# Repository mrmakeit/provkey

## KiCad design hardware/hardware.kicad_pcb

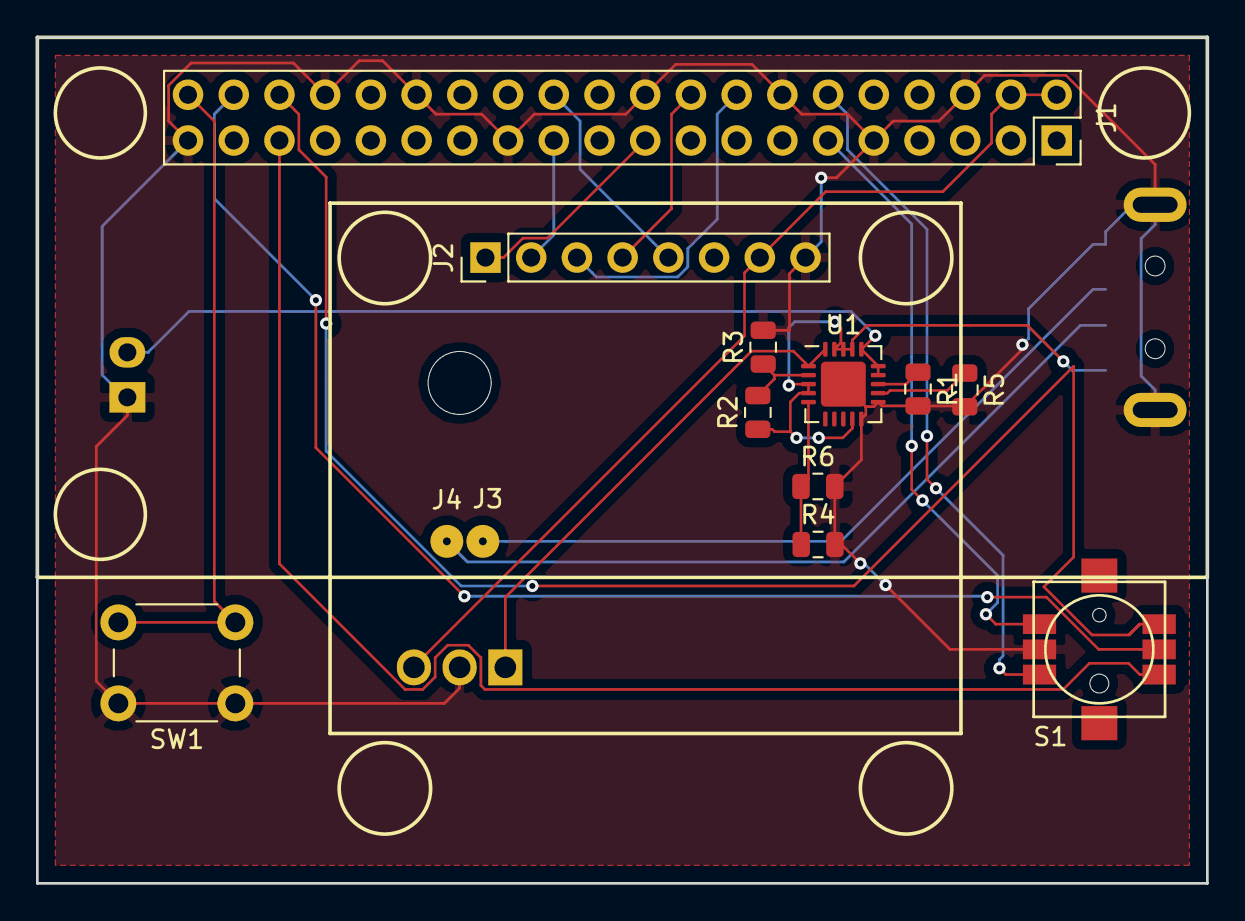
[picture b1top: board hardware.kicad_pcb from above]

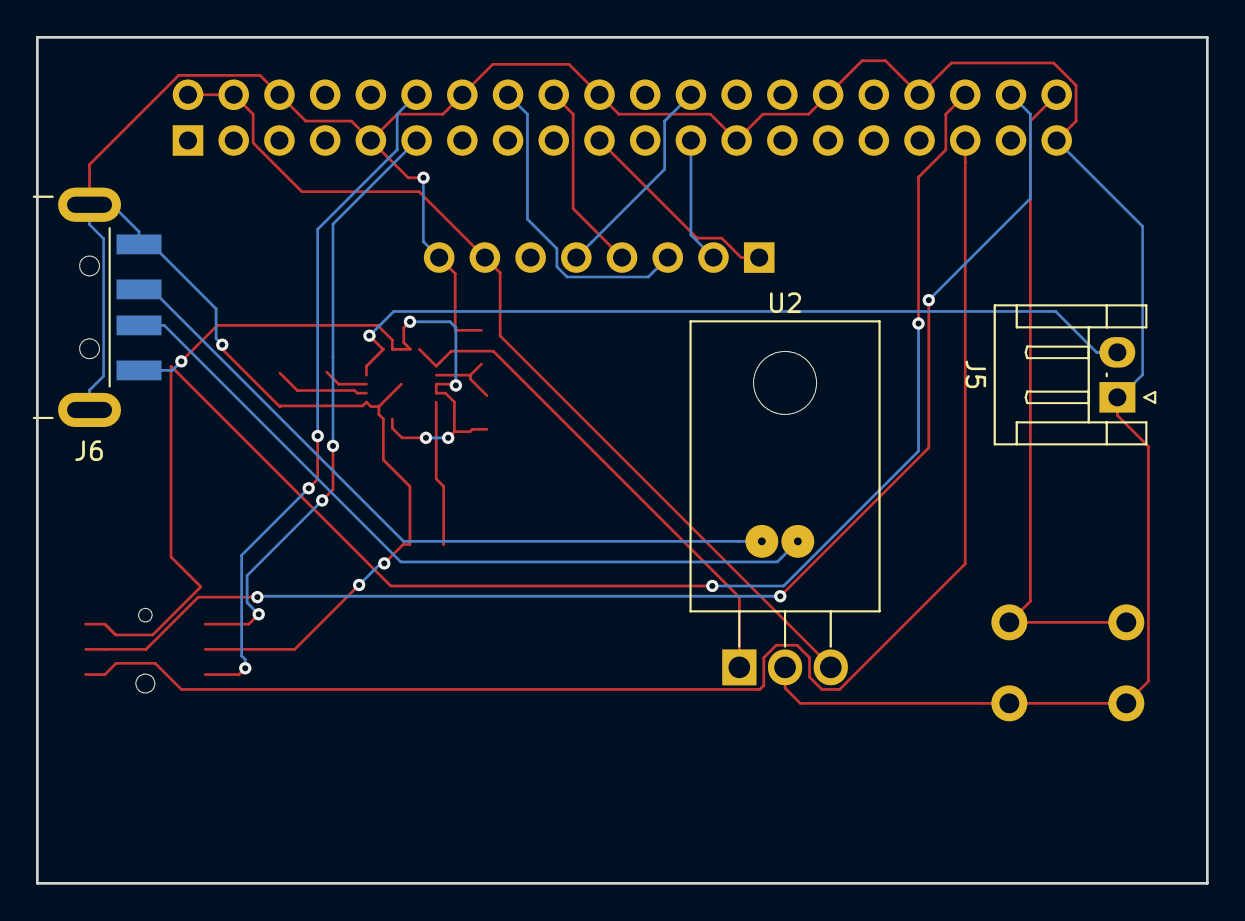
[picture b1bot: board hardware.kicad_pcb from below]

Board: 2 copper layers, 65.0 x 47.0 mm, 16 parts (3 on the bottom side), 22 nets.

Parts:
J1: Raspberry_Pi_2_3; PinSocket_2x20_P2.54mm_Vertical
J2: SSD1608_SPI; PinHeader_1x08_P2.54mm_Vertical
J3, J4: 0906-1; 0906-1-15-20-75
J5: Batt; JST_EH_S02B-EH_1x02_P2.50mm_Horizontal
J6: USB_A; USB_A_CNCTech_1001-011-01101_Horizontal
R1: 2K; R_0805_2012Metric
R2: 270k; R_0805_2012Metric
R3, R5: 100K; R_0805_2012Metric
R4: 10K; R_0805_2012Metric
R6: 150K; R_0805_2012Metric
S1: 5-Way; COM-10063
SW1: SW_MEC_5G; SW_PUSH_6mm
U1: MCP73871; QFN-20-1EP_4x4mm_P0.5mm_EP2.5x2.5mm
U2: L7805; TO-220F-3_Horizontal_TabDown

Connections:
+5V: J1.2, J1.4, J2.7, U2.3
/OLED_CS: J1.24, J2.5
/SPI_CLK: J1.23, J2.2
/SPI_DC: J1.16, J2.3
/SPI_MOSI: J1.19, J2.1
/SPI_RESET: J1.18, J2.4
GND: J1.6, J1.9, J1.14, J1.20, J1.25, J1.30, J1.34, J1.39, J2.8, J5.1, J6.4, J6.5, R1.2, R3.2, R4.2, R5.2, R6.2, S1.5, SW1.1, U1.10, U1.11, U1.21, U2.2
unnamed: J1.11, S1.4
unnamed: J1.12, S1.6
unnamed: J1.35, S1.3
unnamed: J1.36, S1.1
unnamed: J1.38, S1.2
unnamed: J1.40, SW1.2
unnamed: J3.1, J6.3
unnamed: J4.1, J6.2
unnamed: J5.2, U1.14, U1.15, U1.16
unnamed: R1.1, U1.13
unnamed: R2.2, R3.1, U1.2
unnamed: R4.1, R6.1, U1.5
unnamed: R5.1, U1.12
unnamed: U1.1, U1.20, U2.1
VBUS: J6.1, R2.1, U1.3, U1.4, U1.9, U1.17, U1.18, U1.19

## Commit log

2018-10-28 update pcb
